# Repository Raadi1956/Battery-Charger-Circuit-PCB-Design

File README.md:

# Battery-Charger-Circuit-PCB-Design
A PCB design for a battery charging circuit using scr and zener diode

#5V regulated power supply
this project integrates a SCR to regulate the AC source to a DC to charger electronic gadgets or power other modules like esp, uno, etc

#Features and working
1. stepped-down input through a transformer of rated voltage and current as per the circuit requirements through screw terminal connectors.
2. use of full wave rectifier with smoothening filters
3. a triggered SCR for safe regulation of power by its gate current
4. 5.1V zener diode to give a stable voltage output
5. TIP122 power transistor to amplify current to provide stable power to any gadget.
6. output via USB A port

#Components
1. terminal screw connector
2. diodes(1N4007)
3. 5.1V Zener diode
4. TYN612 SCR
5. TIP122
6. 100u polarised capacitor
7. gate resistor (500 ohms)
8. USB A port

#Designed using KiCAD

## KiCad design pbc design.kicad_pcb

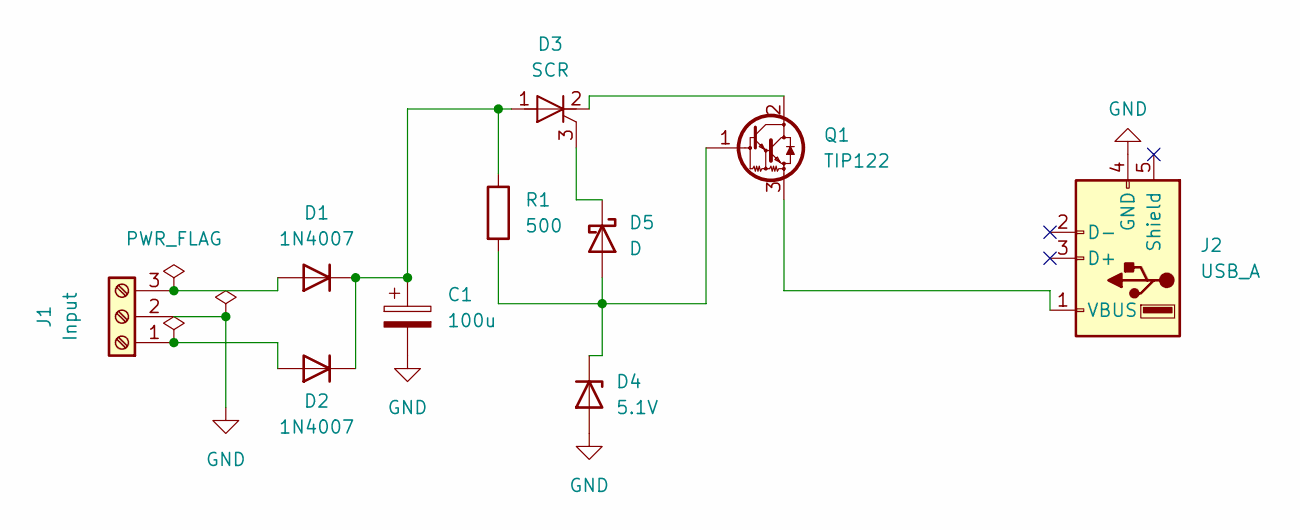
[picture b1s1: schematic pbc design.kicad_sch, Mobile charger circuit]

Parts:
C1: 100u; CP_Radial_D12.5mm_P7.50mm
D1, D2: 1N4007; D_DO-41_SOD81_P10.16mm_Horizontal
D3: SCR; TO-220F-3_Vertical
D4: 5.1V; D_DO-35_SOD27_P10.16mm_Horizontal
D5: D; D_DO-41_SOD81_P10.16mm_Horizontal
J1: Input; TerminalBlock_MetzConnect_Type175_RT02703HBLC_1x03_P7.50mm_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
J2: USB_A; USB_A_TE_292303-7_Horizontal
Q1: TIP122; TO-220-3_Vertical
R1: 500; R_Axial_DIN0207_L6.3mm_D2.5mm_P7.62mm_Horizontal

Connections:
GND: C1.2, D4.2 (A), J1.2, J2.4 (GND)
unnamed: D1.2 (A), J1.3
unnamed: C1.1, D1.1 (K), D2.1 (K), D3.1 (A), R1.1
unnamed: D2.2 (A), J1.1
unnamed: D3.3 (G), D5.1 (K)
unnamed: D3.2 (K), Q1.2 (C)
unnamed: D4.1 (K), D5.2 (A), Q1.1 (B), R1.2
unnamed: J2.1 (VBUS), Q1.3 (E)

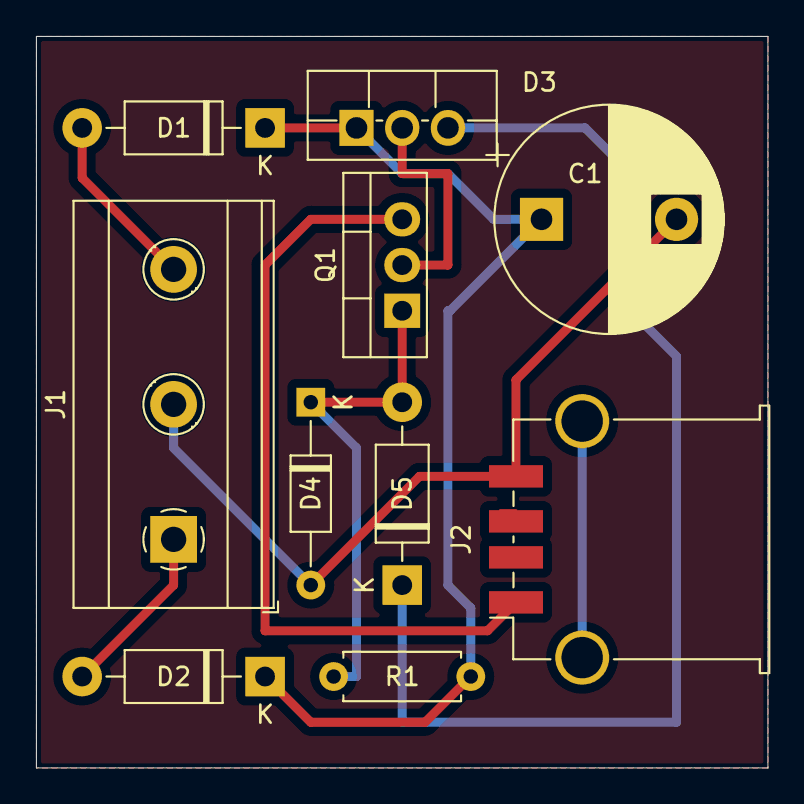
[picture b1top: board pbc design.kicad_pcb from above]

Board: 2 copper layers, 40.6 x 40.6 mm, 10 parts (0 on the bottom side), 8 nets.

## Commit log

2025-07-18 README.md
